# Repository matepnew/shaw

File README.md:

# SHAW!
Devboard based on the Blueprint guides to learn basics of electronics and PCB design.
 
## PCB
### Schematic

### PCB layout

### 3D Model

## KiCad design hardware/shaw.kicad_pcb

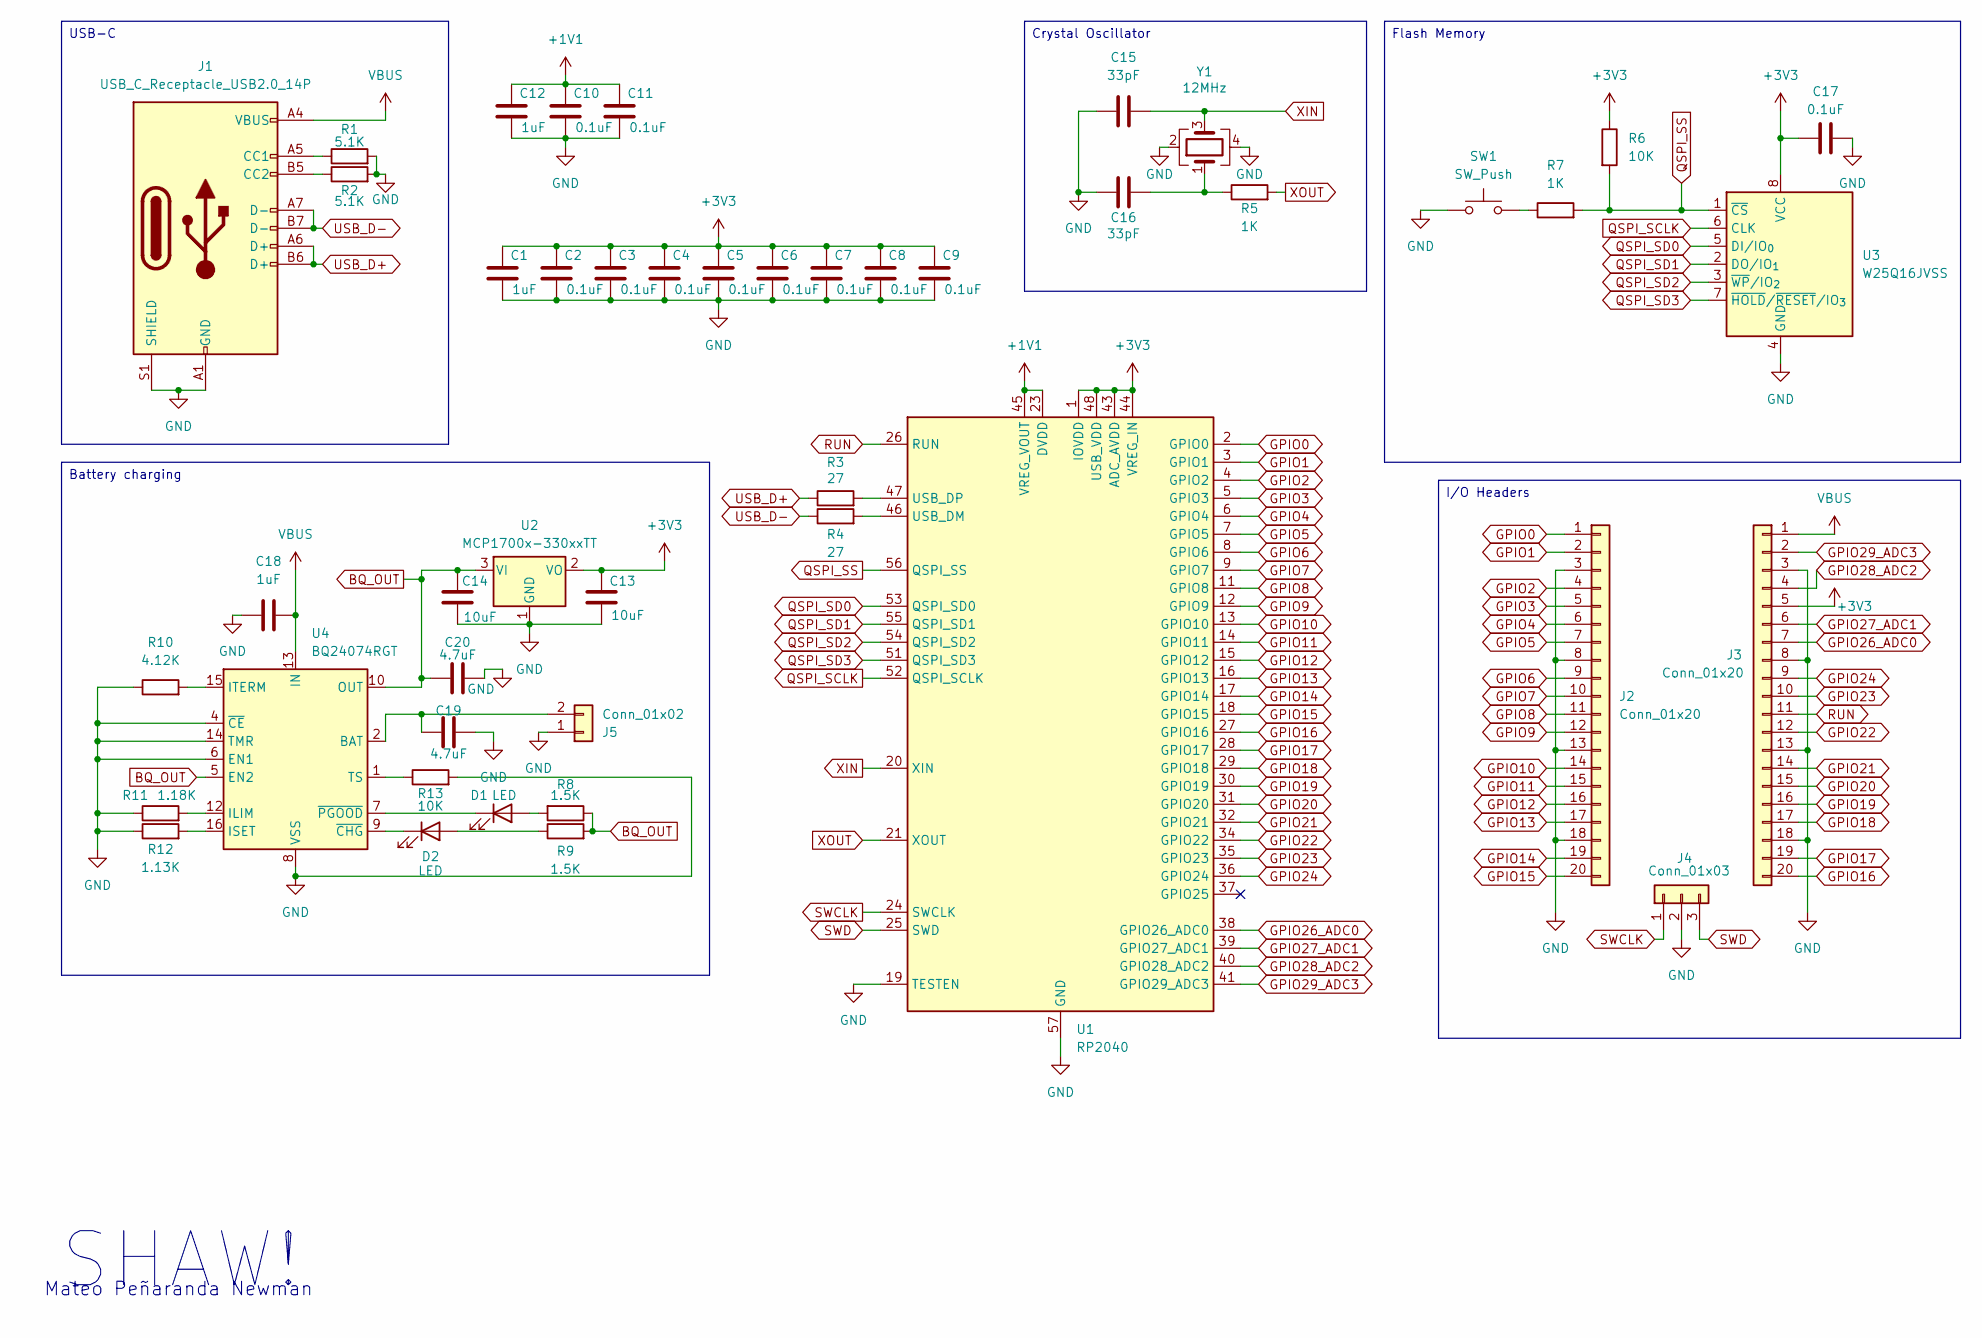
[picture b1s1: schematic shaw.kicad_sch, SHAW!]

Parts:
C1, C12, C18: 1uF; C_0402_1005Metric
C2, C3, C4, C5, C6, C7, C8, C9, C10, C11, C17: 0.1uF; C_0402_1005Metric
C13, C14: 10uF; C_0603_1608Metric
C15, C16: 33pF; C_0402_1005Metric
C19, C20: 4.7uF; C_0603_1608Metric
D1, D2: LED; LED_0402_1005Metric
J1: USB_C_Receptacle_USB2.0_14P; USB_C_Receptacle_HRO_TYPE-C-31-M-12
J2, J3: Conn_01x20; PinHeader_1x20_P2.54mm_Vertical
J4: Conn_01x03; PinHeader_1x03_P2.54mm_Vertical
J5: Conn_01x02; JST_EH_B2B-EH-A_1x02_P2.50mm_Vertical
R1, R2: 5.1K; R_0402_1005Metric
R3, R4: 27; R_0402_1005Metric
R5, R7: 1K; R_0402_1005Metric
R6, R13: 10K; R_0402_1005Metric
R8, R9: 1.5K; R_0402_1005Metric
R10: 4.12K; R_0402_1005Metric
R11: 1.18K; R_0402_1005Metric
R12: 1.13K; R_0402_1005Metric
SW1: SW_Push; SW_Push_SPST_NO_Alps_SKRK
U1: RP2040; QFN-56-1EP_7x7mm_P0.4mm_EP3.2x3.2mm
U2: MCP1700x-330xxTT; SOT-23
U3: W25Q16JVSS; Winbond_USON-8-1EP_3x2mm_P0.5mm_EP0.2x1.6mm
U4: BQ24074RGT; VQFN-16-1EP_3x3mm_P0.5mm_EP1.6x1.6mm
Y1: 12MHz; Crystal_SMD_3225-4Pin_3.2x2.5mm

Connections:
+1V1: C10.1, C11.1, C12.1, U1.23 (DVDD), U1.45 (VREG_VOUT), U1.50 (DVDD)
+3V3: C1.1, C2.1, C3.1, C4.1, C5.1, C6.1, C7.1, C8.1, C9.1, C13.1, C17.1, J3.5, R6.1, U1.1 (IOVDD), U1.10 (IOVDD), U1.22 (IOVDD), U1.33 (IOVDD), U1.42 (IOVDD), U1.43 (ADC_AVDD), U1.44 (VREG_IN), U1.48 (USB_VDD), U1.49 (IOVDD), U2.2 (VO), U3.8 (VCC)
BQ_OUT: C14.1, C20.1, R8.1, R9.2, U2.3 (VI), U4.5 (EN2), U4.10 (OUT), U4.11 (OUT)
GND: C1.2, C2.2, C3.2, C4.2, C5.2, C6.2, C7.2, C8.2, C9.2, C10.2, C11.2, C12.2, C13.2, C14.2, C15.1, C16.2, C17.2, C18.1, C19.2, C20.2, J1.A1 (GND), J1.A12 (GND), J1.B1 (GND), J1.B12 (GND), J1.S1 (SHIELD), J2.3, J2.8, J2.13, J2.18, J3.3, J3.8, J3.13, J3.18, J4.2, J5.1, R1.2, R2.2, R10.1, R11.1, R12.1, R13.2, SW1.1, U1.19 (TESTEN), U1.57 (GND), U2.1 (GND), U3.4 (GND), U4.4 (~CE), U4.6 (EN1), U4.8 (VSS), U4.14 (TMR), U4.17 (VSS), Y1.2, Y1.4
GPIO0: J2.1, U1.2 (GPIO0)
GPIO1: J2.2, U1.3 (GPIO1)
GPIO2: J2.4, U1.4 (GPIO2)
GPIO3: J2.5, U1.5 (GPIO3)
GPIO4: J2.6, U1.6 (GPIO4)
GPIO5: J2.7, U1.7 (GPIO5)
GPIO6: J2.9, U1.8 (GPIO6)
GPIO7: J2.10, U1.9 (GPIO7)
GPIO8: J2.11, U1.11 (GPIO8)
GPIO9: J2.12, U1.12 (GPIO9)
GPIO10: J2.14, U1.13 (GPIO10)
GPIO11: J2.15, U1.14 (GPIO11)
GPIO12: J2.16, U1.15 (GPIO12)
GPIO13: J2.17, U1.16 (GPIO13)
GPIO14: J2.19, U1.17 (GPIO14)
GPIO15: J2.20, U1.18 (GPIO15)
GPIO16: J3.20, U1.27 (GPIO16)
GPIO17: J3.19, U1.28 (GPIO17)
GPIO18: J3.17, U1.29 (GPIO18)
GPIO19: J3.16, U1.30 (GPIO19)
GPIO20: J3.15, U1.31 (GPIO20)
GPIO21: J3.14, U1.32 (GPIO21)
GPIO22: J3.12, U1.34 (GPIO22)
GPIO23: J3.10, U1.35 (GPIO23)
GPIO24: J3.9, U1.36 (GPIO24)
GPIO26_ADC0: J3.7, U1.38 (GPIO26_ADC0)
GPIO27_ADC1: J3.6, U1.39 (GPIO27_ADC1)
GPIO28_ADC2: J3.4, U1.40 (GPIO28_ADC2)
GPIO29_ADC3: J3.2, U1.41 (GPIO29_ADC3)
unnamed: C16.1, R5.1, Y1.1
unnamed: D1.2 (A), R8.2
unnamed: D1.1 (K), U4.7 (~PGOOD)
unnamed: D2.2 (A), R9.1
unnamed: D2.1 (K), U4.9 (~CHG)
unnamed: J1.A5 (CC1), R1.1
unnamed: J1.B5 (CC2), R2.1
unnamed: C19.1, J5.2, U4.2 (BAT), U4.3 (BAT)
unnamed: R7.1, SW1.2
unnamed: R4.2, U1.46 (USB_DM)
unnamed: R3.2, U1.47 (USB_DP)
unnamed: R11.2, U4.12 (ILIM)
unnamed: R12.2, U4.16 (ISET)
unnamed: R10.2, U4.15 (ITERM)
unnamed: R13.1, U4.1 (TS)
QSPI_SCLK: U1.52 (QSPI_SCLK), U3.6 (CLK)
QSPI_SD0: U1.53 (QSPI_SD0), U3.5 (DI/IO_{0})
QSPI_SD1: U1.55 (QSPI_SD1), U3.2 (DO/IO_{1})
QSPI_SD2: U1.54 (QSPI_SD2), U3.3 (~WP/IO_{2})
QSPI_SD3: U1.51 (QSPI_SD3), U3.7 (~HOLD/~RESET/IO_{3})
QSPI_SS: R6.2, R7.2, U1.56 (QSPI_SS), U3.1 (~CS)
RUN: J3.11, U1.26 (RUN)
SWCLK: J4.1, U1.24 (SWCLK)
SWD: J4.3, U1.25 (SWD)
USB_D+: J1.A6 (D+), J1.B6 (D+), R3.1
USB_D-: J1.A7 (D-), J1.B7 (D-), R4.1
VBUS: C18.2, J1.A4 (VBUS), J1.A9 (VBUS), J1.B4 (VBUS), J1.B9 (VBUS), J3.1, U4.13 (IN)
XIN: C15.2, U1.20 (XIN), Y1.3
XOUT: R5.2, U1.21 (XOUT)

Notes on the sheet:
SHAW!
Mateo Peñaranda Newman
Flash Memory
USB-C
Battery charging
Crystal Oscillator
I/O Headers

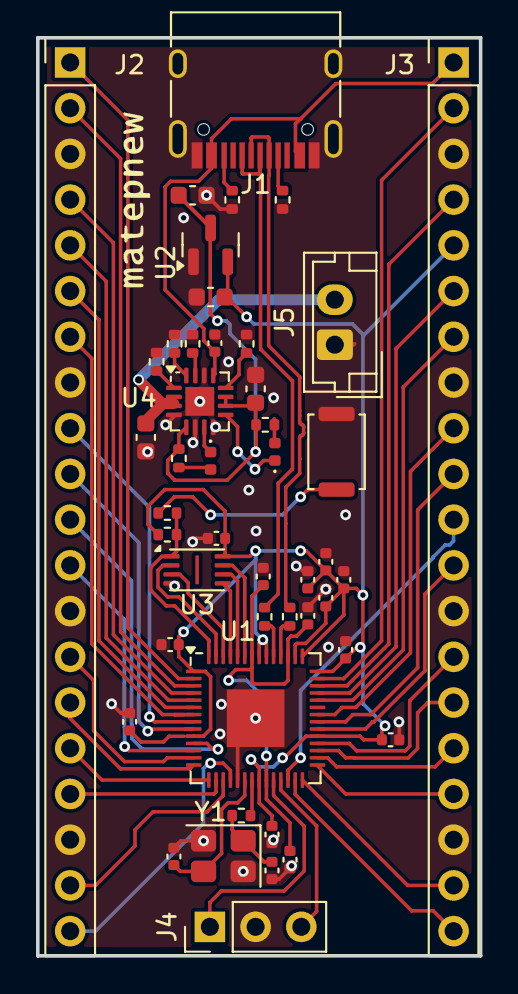
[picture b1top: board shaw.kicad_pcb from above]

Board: 2 copper layers, 24.6 x 51.0 mm, 46 parts (0 on the bottom side), 62 nets.

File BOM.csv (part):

JLCPCB BOM Tool - BOM Matching,,,,,,,,,,,,,,,,,
BOM name：bom-JLCPCB Assembly Order.xlsx,,,Download Time：2025-11-09 06:44:54,,,,"* Our matching results are updated in real-time, but stock and prices may change. 
If it's been over 24 hours, please re-match before placing your order.",,,,,,,,,,
PCB Assembled Qty：5,,,Est. Total Price：25.8304,,,,,,,,,,,,,,
Your BOM,,,,,Matched Parts,,,,,,,Order Information,,,,,
Top Designator,Bottom Designator,Comment,Footprint,JLCPCB Part #,Matches,Part # ,Manufacturer,Footprint,Description,Category,Warning,JLCPCB Part #,Product link,Lib Type,Qty,Source,Total Price ($)
"C1,C12,C18",,1uF,0402,,Select by System,CL05A105KA5NQNC,Samsung Electro-Mechanics,0402,1uF 25V X5R ±10% 0402 Multilayer Ceramic Capacitors MLCC - SMD/SMT ROHS,Multilayer Ceramic Capacitors MLCC - SMD/SMT,,C52923,https://jlcpcb.com/partdetail/53938-CL05A105KA5NQNC/C52923,Basic,15,15 JLCPCB,0.0435
"C10,C11,C17,C2,C3,C4,C5,C6,C7,C8,C9",,0.1uF,0402,,Unconfirmed,CL05B104KB54PNC,Samsung Electro-Mechanics,0402,100nF 50V X7R ±10% 0402 Multilayer Ceramic Capacitors MLCC - SMD/SMT ROHS,Multilayer Ceramic Capacitors MLCC - SMD/SMT,1.The comment (CL05B104KB54PNC) of this part does not match the one (0.1uF) provided in your BOM. Please confirm;,C307331,https://jlcpcb.com/partdetail/291005-CL05B104KB54PNC/C307331,Basic,55,55 JLCPCB,0.22
"C13,C14",,10uF,0603,,Select by System,CL10A106KP8NNNC,Samsung Electro-Mechanics,0603,10V 10uF X5R ±10% 0603 Multilayer Ceramic Capacitors MLCC - SMD/SMT ROHS,Multilayer Ceramic Capacitors MLCC - SMD/SMT,,C19702,https://jlcpcb.com/partdetail/20411-CL10A106KP8NNNC/C19702,Basic,10,10 JLCPCB,0.056
"C15,C16",,33pF,0402,,Select by System,0402CG330J500NT,FH (Guangdong Fenghua Advanced Tech),0402,33pF 50V C0G ±5% 0402 Multilayer Ceramic Capacitors MLCC - SMD/SMT ROHS,Multilayer Ceramic Capacitors MLCC - SMD/SMT,,C1562,https://jlcpcb.com/partdetail/1914-0402CG330J500NT/C1562,Basic,10,10 JLCPCB,0.01
"C19,C20",,4.7uF,0603,,Select by System,CL10A475KO8NNNC,Samsung Electro-Mechanics,0603,16V 4.7uF X5R ±10% 0603 Multilayer Ceramic Capacitors MLCC - SMD/SMT ROHS,Multilayer Ceramic Capacitors MLCC - SMD/SMT,,C19666,https://jlcpcb.com/partdetail/20375-CL10A475KO8NNNC/C19666,Basic,10,10 JLCPCB,0.092
"D1,D2",,LED,0402,,Unconfirmed,XL-1005UGC,XINGLIGHT,0402,-40℃~+85℃ 120° 249mcd 25mA 3V 516nm~531nm 531nm 80mW Emerald Green Water Clear op View Mount 0402 LED Indication - Discrete ROHS,LED Indication - Discrete,1.The comment (XL-1005UGC) of this part does not match the one (LED) provided in your BOM. Please confirm;,C965793,https://jlcpcb.com/partdetail/XINGLIGHT-XL1005UGC/C965793,Extended,22,22 JLCPCB,0.1474
J1,,USB_C_Receptacle_USB2.0_14P,USB_C_Receptacle_HRO_TYPE-C-31-M-12,,Select by Customer,TYPE-C-31-M-12,Korean Hroparts Elec,SMD,1 16P 5A Female Type-C SMD USB Connectors ROHS,USB Connectors,,C165948,https://jlcpcb.com/partdetail/Korean_HropartsElec-TYPE_C_31_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,Extended,5,5 JLCPCB,0.847
"J2,J3",,Conn_01x20,PinHeader_1x20_P2.54mm_Vertical,,Select by Customer,2.54-1*20P直针,BOOMELE(Boom Precision Elec),"插件,P=2.54mm","-40℃~+105℃ 1 1x20P 2.54mm 20P 3A Black Brass Pin Header Through Hole Plugin,P=2.54mm Pin Headers ROHS",Pin Headers,,C50981,https://jlcpcb.com/partdetail/51993-2_54_1_20P/C50981,Extended,0,0 JLCPCB,0
J4,,Conn_01x03,PinHeader_1x03_P2.54mm_Vertical,,Select by Customer,2.54-1*3P针,BOOMELE(Boom Precision Elec),"插件,P=2.54mm","-40℃~+105℃ 1 1x3P 2.54mm 2.5mm 3A 3P 3mm 6mm Black Brass Gold Pin Header Through Hole Plugin,P=2.54mm Pin Headers ROHS",Pin Headers,,C49257,https://jlcpcb.com/partdetail/50265-2_54_1_3P/C49257,Extended,0,0 JLCPCB,0
J5,,Conn_01x02,JST_EH_B2B-EH-A_1x02_P2.50mm_Vertical,,Select by Customer,B2B-EH-A(LF)(SN),JST,"插件,P=2.5mm","-25℃~+85℃ 1 1x2P 2 2.5mm 250V 2P 3.8mm 3A 6mm 7.5mm Brass EH PA66 Through Hole Tin UL94V-0 White Plugin,P=2.5mm Wire To Board Connector ROHS",Wire To Board Connector,,C160262,https://jlcpcb.com/partdetail/JST-B2B_EH_A_LF_SN/C160262,Extended,9,9 JLCPCB,0.3393
"R1,R2",,5.1K,0402,,Unconfirmed,0402WGF5101TCE,UNI-ROYAL(Uniroyal Elec),0402,-55℃~+155℃ 5.1kΩ 50V 62.5mW Thick Film Resistor ±1% ±100ppm/℃ 0402 Chip Resistor - Surface Mount ROHS,Chip Resistor - Surface Mount,1.The comment (0402WGF5101TCE) of this part does not match the one (5.1K) provided in your BOM. Please confirm;,C25905,https://jlcpcb.com/partdetail/26648-0402WGF5101TCE/C25905,Basic,10,10 JLCPCB,0.005
"R3,R4",,27,0402,,Unconfirmed,0402WGF270JTCE,UNI-ROYAL(Uniroyal Elec),0402,-55℃~+155℃ 27Ω 50V 62.5mW Thick Film Resistor ±1% ±100ppm/℃ 0402 Chip Resistor - Surface Mount ROHS,Chip Resistor - Surface Mount,1.The comment (0402WGF270JTCE) of this part does not match the one (27) provided in your BOM. Please confirm;,C25100,https://jlcpcb.com/partdetail/25843-0402WGF270JTCE/C25100,Extended,22,22 JLCPCB,0.0132
"R5,R7",,1K,0402,,Unconfirmed,0402WGF1001TCE,UNI-ROYAL(Uniroyal Elec),0402,-55℃~+155℃ 1kΩ 50V 62.5mW Thick Film Resistor ±1% ±100ppm/℃ 0402 Chip Resistor - Surface Mount ROHS,Chip Resistor - Surface Mount,1.The comment (0402WGF1001TCE) of this part does not match the one (1K) provided in your BOM. Please confirm;,C11702,https://jlcpcb.com/partdetail/12256-0402WGF1001TCE/C11702,Basic,10,10 JLCPCB,0.006
"R8,R9",,1.5K,0402,,Unconfirmed,0402WGF1501TCE,UNI-ROYAL(Uniroyal Elec),0402,-55℃~+155℃ 1.5kΩ 50V 62.5mW Thick Film Resistor ±1% ±100ppm/℃ 0402 Chip Resistor - Surface Mount ROHS,Chip Resistor - Surface Mount,1.The comment (0402WGF1501TCE) of this part does not match the one (1.5K) provided in your BOM. Please confirm;,C25867,https://jlcpcb.com/partdetail/26610-0402WGF1501TCE/C25867,Basic,10,10 JLCPCB,0.006
R10,,4.12K,0402,,Unconfirmed,RC0402FR-074K12L,YAGEO,0402,-55℃~+155℃ 4.12kΩ 50V 62.5mW Thick Film Resistor ±1% ±100ppm/℃ 0402 Chip Resistor - Surface Mount ROHS,Chip Resistor - Surface Mount,1.The comment (RC0402FR-074K12L) of this part does not match the one (4.12K) provided in your BOM. Please confirm;,C327340,https://jlcpcb.com/partdetail/YAGEO-RC0402FR074K12L/C327340,Extended,20,20 JLCPCB,0.006
R11,,1.18K,0402,,Unconfirmed,0402WGF1181TCE,UNI-ROYAL(Uniroyal Elec),0402,-55℃~+155℃ 1.18kΩ 50V 62.5mW Thick Film Resistor ±1% ±100ppm/℃ 0402 Chip Resistor - Surface Mount ROHS,Chip Resistor - Surface Mount,1.The comment (0402WGF1181TCE) of this part does not match the one (1.18K) provided in your BOM. Please confirm;,C270651,https://jlcpcb.com/partdetail/260031-0402WGF1181TCE/C270651,Extended,20,20 JLCPCB,0.008
R12,,1.13K,0402,,Unconfirmed,0402WGF1131TCE,UNI-ROYAL(Uniroyal Elec),0402,-55℃~+155℃ 1.13kΩ 50V 62.5mW Thick Film Resistor ±1% ±100ppm/℃ 0402 Chip Resistor - Surface Mount ROHS,Chip Resistor - Surface Mount,1.The comment (0402WGF1131TCE) of this part does not match the one (1.13K) provided in your BOM. Please confirm;,C67014,https://jlcpcb.com/partdetail/68102-0402WGF1131TCE/C67014,Extended,20,20 JLCPCB,0.012
"R13,R6",,10K,0402,,Unconfirmed,0402WGF1002TCE,UNI-ROYAL(Uniroyal Elec),0402,-55℃~+155℃ 10kΩ 50V 62.5mW Thick Film Resistor ±1% ±100ppm/℃ 0402 Chip Resistor - Surface Mount ROHS,Chip Resistor - Surface Mount,1.The comment (0402WGF1002TCE) of this part does not match the one (10K) provided in your BOM. Please confirm;,C25744,https://jlcpcb.com/partdetail/26487-0402WGF1002TCE/C25744,Basic,10,10 JLCPCB,0.006
SW1,,SW_Push,SW_Push_SPST_NO_Alps_SKRK,,Select by Customer,TS-1088-AR02016,XUNPU,"SMD,4x3mm","-30℃~+80℃ 1.6N 100,000 Cycles 12V 2mm 3mm 4mm 50mA Black Round Button SMD(SMT) Tab SPST Surface Mount,Vertical Without Bracket SMD,4x3mm Tactile Switches ROHS",Tactile Switches,,C720477,https://jlcpcb.com/partdetail/XUNPU-TS_1088AR02016/C720477,Basic,5,5 JLCPCB,0.2115
U1,,RP2040,QFN-56-1EP_7x7mm_P0.4mm_EP3.2x3.2mm,,Select by Customer,RP2040,Raspberry Pi,LQFN-56(7x7),12bit 133MHz 30 LQFN-56(7x7) Microcontrollers (MCU/MPU/SOC) ROHS,Microcontrollers (MCU/MPU/SOC),,C2040,https://jlcpcb.com/partdetail/RaspberryPi-RP2040/C2040,Extended,5,5 JLCPCB,4.5825
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
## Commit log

2025-11-08 Update README with PCB details and images
    Added PCB schematic, layout, and 3D model images.
2025-11-09 update bom
2025-11-13 Replace bom
